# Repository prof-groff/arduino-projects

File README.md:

# arduino-projects

### makeToneBoard Parts List

* 1 x 28-pin DIP Atmel ATmega328p Microcontroller
* 1 x 28-pin DIP socket
* 1 x 7805 5-V linear voltage regulator
* 1 x Lite-On 4301-package 7-segment display
* 1 x 16 MHz Crystal
* 1 x SPST tactile switch/button, normally open, momentarily closed
* 1 x SPDT slide switch
* 1 x 2 rows, 6 positions header
* 1 x female 2.1 mm barrel jack
* 1 x black female banana plug jack
* 1 x red female banana plug jack
* 1 x 300 ohm resistor, 0.25W
* 7 x 110 ohm resistor, 0.25W
* 2 x 100 kohm resistor, 0.25W
* 2 x 22 pF ceramic capacitor, 100V
* 1 x 0.1 microF ceramic capacitor, 50V
* 1 x 0.33 microF ceramic capacitor, 50V

### WaveFormIO Parts List

* Motorola/Freescale MC14489B
* Lite-On LTC-4727JR 4-Digit Display
* ATmega 328P-PU
* 7805
* PTV09A-2020F-A502 Bourns 5k Poteniometer
* PTV09A-2020F-A103 Bourns 10k Poteniometer
* Push Button - Momentary On - Schurter 1301.9305
* E-Switch EG2301A (6mm-tall switch arm)
* 108-0903-001 (Black)
* 108-0902-001 (Red)
* Op-Amp for voltage follower
* TE Connectivity 1-971111-3 Flat Cable 10C 28AWG
* 3365/10-CUT-LENGTH 3M
* OMRON XG4M-1030-T Cable Crip Connector Female
* OMRON XG4C-1031 PCB Socket Male

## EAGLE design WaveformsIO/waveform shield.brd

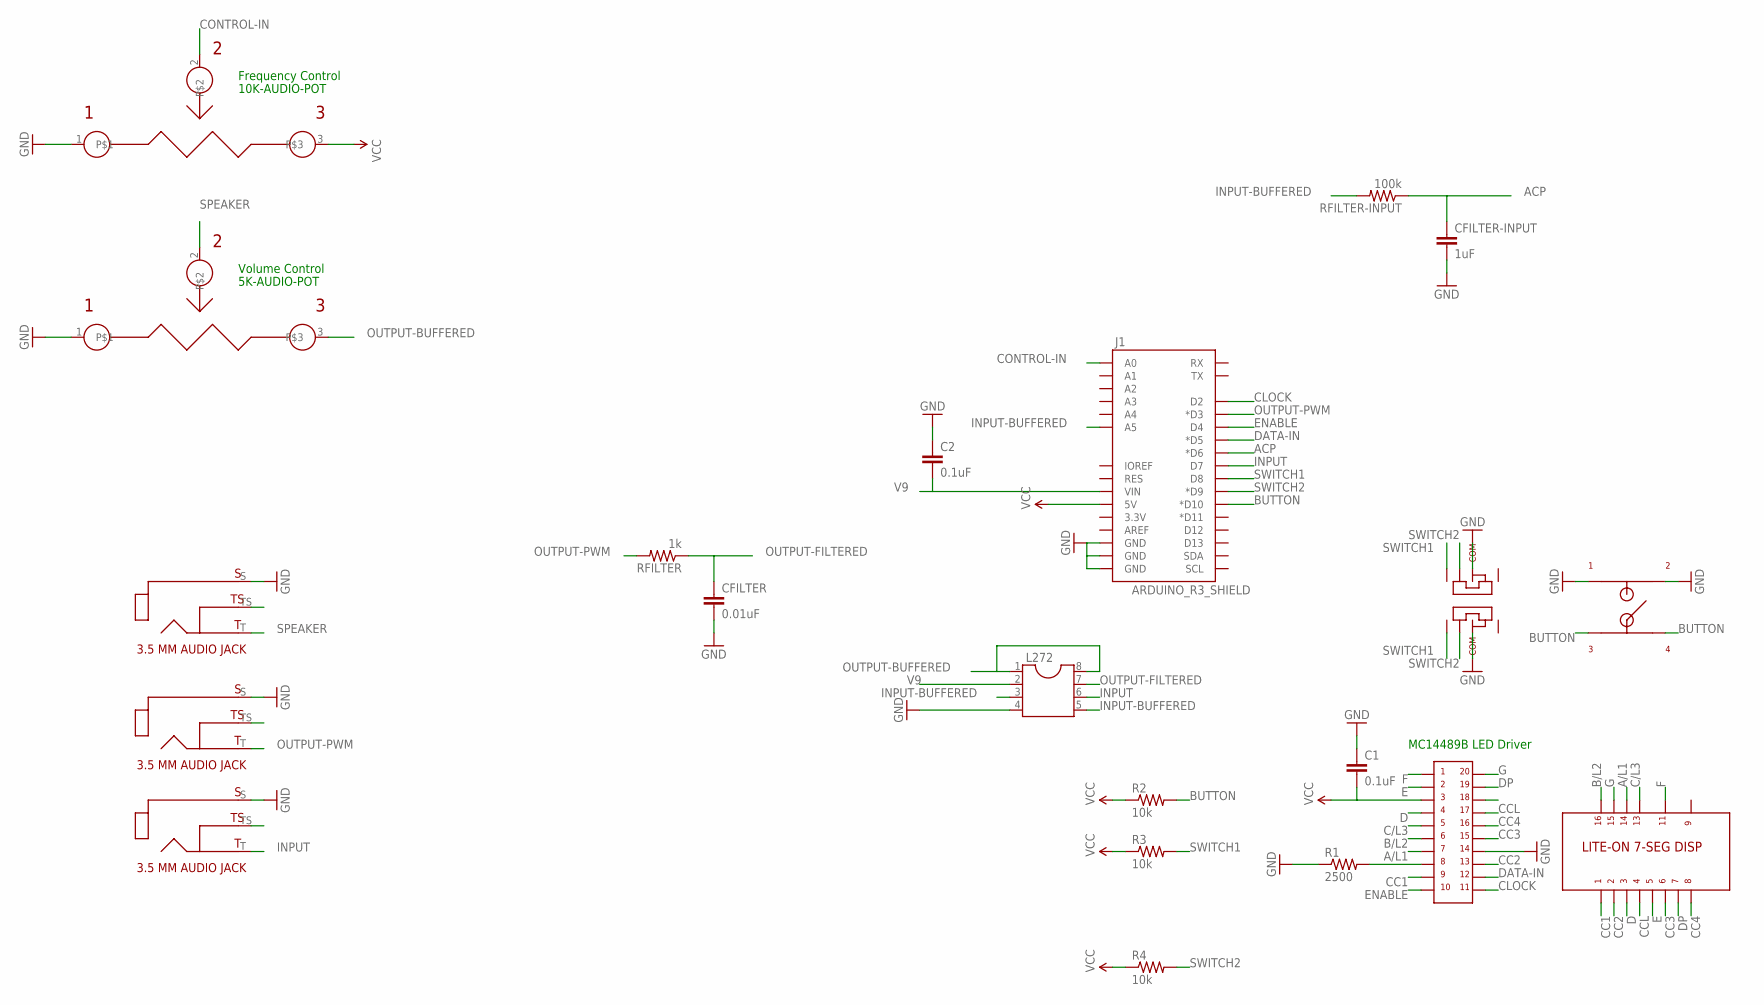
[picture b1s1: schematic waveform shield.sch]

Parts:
5K-AUDIO-POT: BOURNS-PTV09A-2; BOURNS-POT-PTV09A-2
C1, C2: 0.1uF; CAP-PTH-SMALL
CFILTER: 0.01uF; CAP-PTH-SMALL
CFILTER-INPUT: 1uF; CAP-PTH-SMALL
J1: ARDUINO_R3_SHIELD; UNO_R3_SHIELD
L272: DIL8; DIL08
R1: 2500; AXIAL-0.3
R2, R3, R4: 10k; AXIAL-0.3
RFILTER: 1k; AXIAL-0.3
RFILTER-INPUT: 100k; AXIAL-0.3
U$1: LITE-ON-7-SEG-DISP; 7-SEG-DISPLAY-LITE-ON
U$2: MC14489B-LED-DRIVER; DIP-20
U$3, U$6, U$7: 3.5MM-AUDIO-JACK-CUI; 3.5MM-AUDIO-JACK-MONO-CUI
U$4: E-SWITCH-THREE-WAY-SWITCH; EG2301-SLIDE-SWITCH
U$5: SWITCH-MOMENTARY-ON-SCHURTER
U$9: BOURNS-PTV09A-2; BOURNS-POT-PTV09A-2

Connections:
A/L1: U$1.P$14, U$2.P$7
ACP: CFILTER-INPUT.1, J1.D6 (*D6), RFILTER-INPUT.P$1 (1)
B/L2: U$1.P$16, U$2.P$6
BUTTON: J1.D10 (*D10), R2.P$2 (2), U$5.P$3, U$5.P$4
C/L3: U$1.P$13, U$2.P$5
CC1: U$1.P$1, U$2.P$9
CC2: U$1.P$2, U$2.P$13
CC3: U$1.P$6, U$2.P$15
CC4: U$1.P$8, U$2.P$16
CCL: U$1.P$4, U$2.P$17
CLOCK: J1.D2, U$2.P$11
CONTROL-IN: J1.A0, U$9.2
D: U$1.P$3, U$2.P$4
DATA-IN: J1.D5 (*D5), U$2.P$12
DP: U$1.P$7, U$2.P$19
E: U$1.P$5, U$2.P$2
ENABLE: J1.D4, U$2.P$10
F: U$1.P$11, U$2.P$1
G: U$1.P$15, U$2.P$20
GND: 5K-AUDIO-POT.1, C1.1, C2.1, CFILTER.2, CFILTER-INPUT.2, J1.GND@0 (GND), J1.GND@1 (GND), J1.GND@2 (GND), L272.4, R1.P$1 (1), U$2.P$14, U$3.S, U$4.P$3, U$4.P$7, U$5.P$1, U$5.P$2, U$6.S, U$7.S, U$9.1
INPUT: J1.D7, L272.6, U$7.T
INPUT-BUFFERED: J1.A5, L272.3, L272.5, RFILTER-INPUT.P$2 (2)
unnamed: R1.P$2 (2), U$2.P$8
OUTPUT-BUFFERED: 5K-AUDIO-POT.3, L272.1, L272.8
OUTPUT-FILTERED: CFILTER.1, L272.7, RFILTER.P$1 (1)
OUTPUT-PWM: J1.D3 (*D3), RFILTER.P$2 (2), U$6.T
SPEAKER: 5K-AUDIO-POT.2, U$3.T
SWITCH1: J1.D8, R3.P$2 (2), U$4.P$1, U$4.P$5
SWITCH2: J1.D9 (*D9), R4.P$2 (2), U$4.P$2, U$4.P$6
V9: C2.2, J1.VIN, L272.2
VCC: C1.2, J1.5V, R2.P$1 (1), R3.P$1 (1), R4.P$1 (1), U$2.P$3, U$9.3

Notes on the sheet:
MC14489B LED Driver
5K-AUDIO-POT
10K-AUDIO-POT
Volume Control
Frequency Control

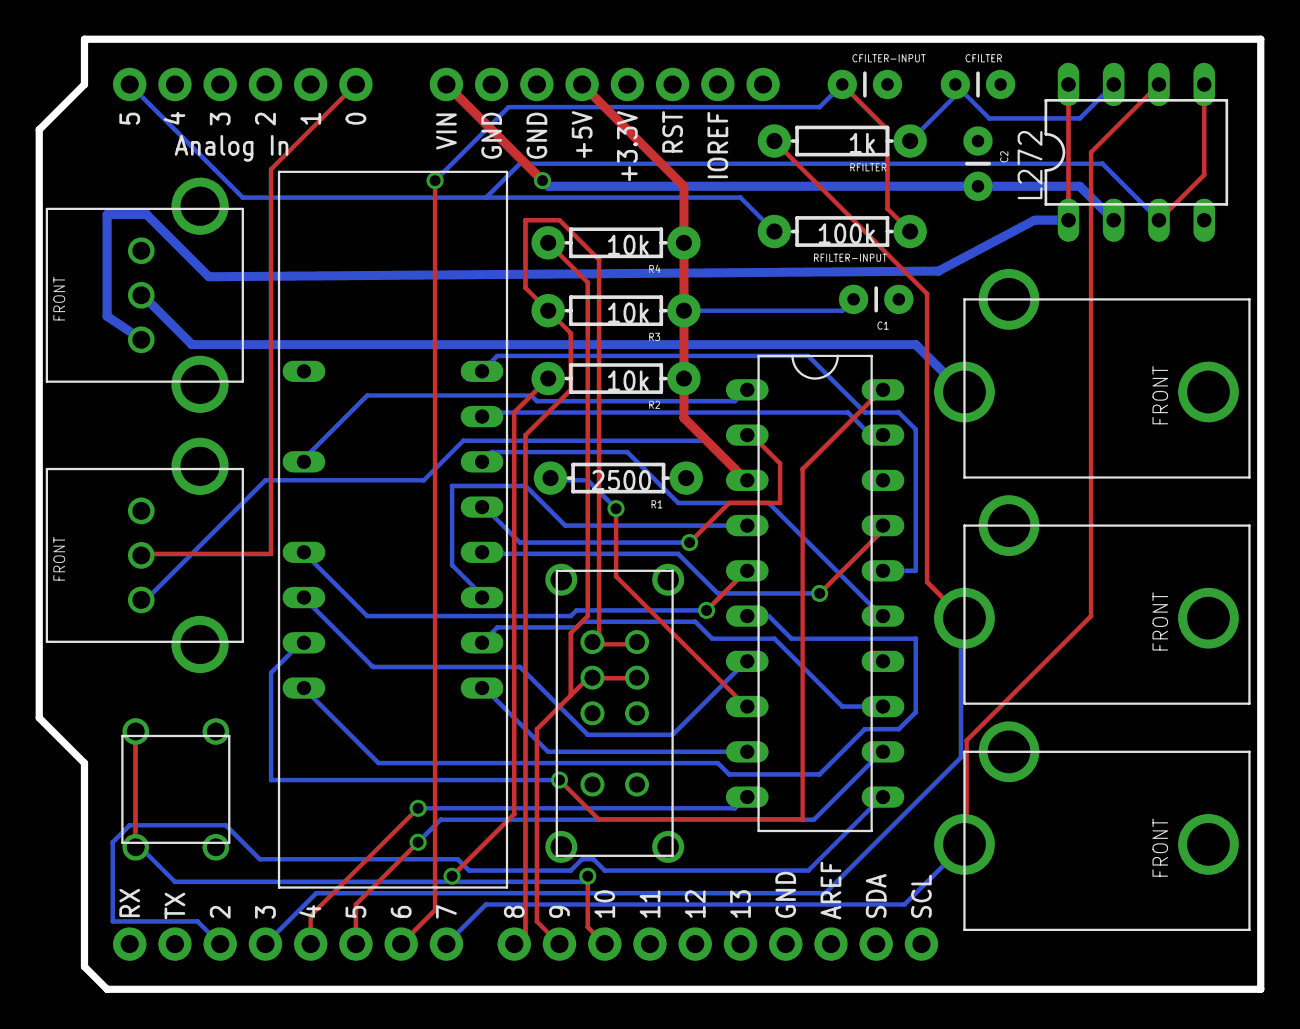
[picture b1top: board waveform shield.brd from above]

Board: 2 copper layers, 68.6 x 53.3 mm, 21 parts (0 on the bottom side), 31 nets.

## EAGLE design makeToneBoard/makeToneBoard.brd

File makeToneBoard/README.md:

# arduino-projects

### makeToneBoard Parts List

* 1 x 28-pin DIP Atmel ATmega328p Microcontroller
* 1 x 28-pin DIP socket
* 1 x 7805 5-V linear voltage regulator
* 1 x Lite-On 4301-package 7-segment display
* 1 x 16 MHz Crystal
* 1 x SPST tactile switch/button, normally open, momentarily closed
* 1 x SPDT slide switch
* 1 x 2 rows, 6 positions header
* 1 x female 2.1 mm barrel jack
* 1 x black female banana plug jack
* 1 x red female banana plug jack
* 1 x 300 ohm resistor, 0.25W
* 7 x 110 ohm resistor, 0.25W
* 2 x 100 kohm resistor, 0.25W
* 2 x 22 pF ceramic capacitor, 100V
* 1 x 0.1 microF ceramic capacitor, 50V
* 1 x 0.33 microF ceramic capacitor, 50V

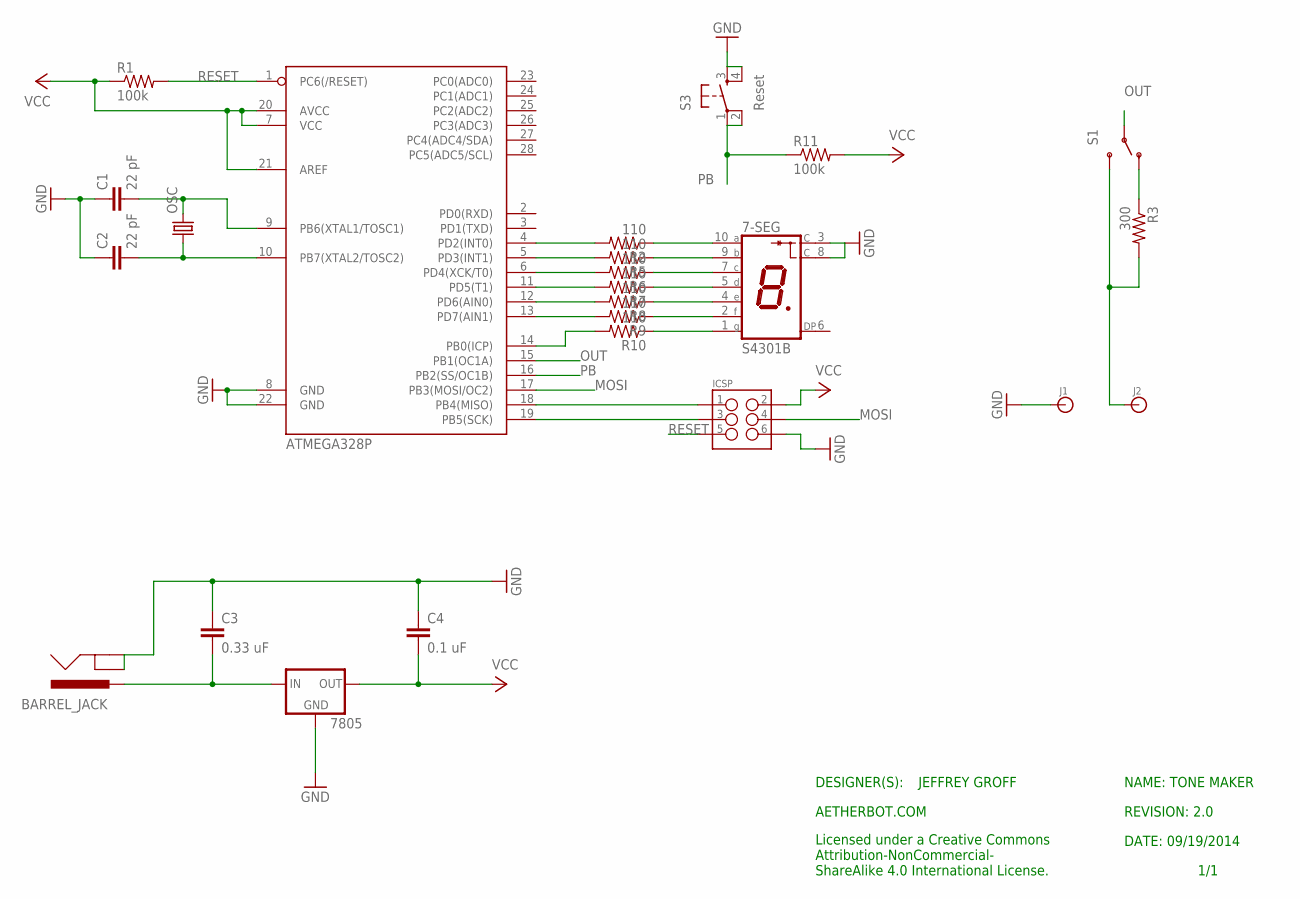
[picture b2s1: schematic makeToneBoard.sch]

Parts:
7-SEG: S4301B
7805: V_REG_78XXSINK; TO220-IGO
BARREL_JACK: POWER_JACKPTH; POWER_JACK_PTH
C1, C2: 22 pF; CAP-PTH-SMALL-KIT
C3: 0.33 uF; CAP-PTH-SMALLEZ
C4: 0.1 uF; CAP-PTH-SMALLEZ
ICSP: M03X2NO_SILK; 2X3-NS
J1, J2: BANANA_CONN
OSC: CRYSTALHC49S; HC49/S
R1, R11: 100k; 0204/7
R2, R5, R6, R7, R8, R9, R10: 110; 0204/7
R3: 300; 0204/7
S1: LED PWR; SWITCH-SPDT
S3: Reset; TACTILE-PTH
U1: ATMEGA328P; DIL28-3

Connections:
GND: 7-SEG.3 (C), 7-SEG.8 (C), 7805.GND, BARREL_JACK.GND, BARREL_JACK.GNDBREAK, C1.1, C2.1, C3.1, C4.1, ICSP.6, J1.P$1, S3.3, S3.4, U1.8 (GND), U1.22 (GND)
MOSI: ICSP.4, U1.17 (PB3(MOSI/OC2))
unnamed: R2.2, U1.4 (PD2(INT0))
unnamed: R3.1, S1.1 (O)
unnamed: J2.P$1, R3.2, S1.3 (S)
unnamed: 7-SEG.1 (G), R10.1
unnamed: C2.2, OSC.1, U1.10 (PB7(XTAL2/TOSC2))
unnamed: 7-SEG.10 (A), R2.1
unnamed: R5.2, U1.5 (PD3(INT1))
unnamed: 7-SEG.9 (B), R5.1
unnamed: R6.2, U1.6 (PD4(XCK/T0))
unnamed: 7805.IN, BARREL_JACK.PWR, C3.2
unnamed: 7-SEG.7 (C), R6.1
unnamed: R7.2, U1.11 (PD5(T1))
unnamed: 7-SEG.5 (D), R7.1
unnamed: ICSP.1, U1.18 (PB4(MISO))
unnamed: ICSP.3, U1.19 (PB5(SCK))
unnamed: R8.2, U1.12 (PD6(AIN0))
unnamed: 7-SEG.4 (E), R8.1
unnamed: R9.2, U1.13 (PD7(AIN1))
unnamed: 7-SEG.2 (F), R9.1
unnamed: R10.2, U1.14 (PB0(ICP))
unnamed: C1.2, OSC.2, U1.9 (PB6(XTAL1/TOSC1))
OUT: S1.2, U1.15 (PB1(OC1A))
PB: R11.1, S3.1, S3.2, U1.16 (PB2(SS/OC1B))
RESET: ICSP.5, R1.2, U1.1 (PC6(/RESET))
VCC: 7805.OUT, C4.2, ICSP.2, R1.1, R11.2, U1.7 (VCC), U1.20 (AVCC), U1.21 (AREF)

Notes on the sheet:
NAME: TONE MAKER
JEFFREY GROFF
DATE: 09/19/2014
DESIGNER(S):
1/1
REVISION: 2.0
AETHERBOT.COM
Licensed under a Creative Commons Attribution-NonCommercial- ShareAlike 4.0 International License.

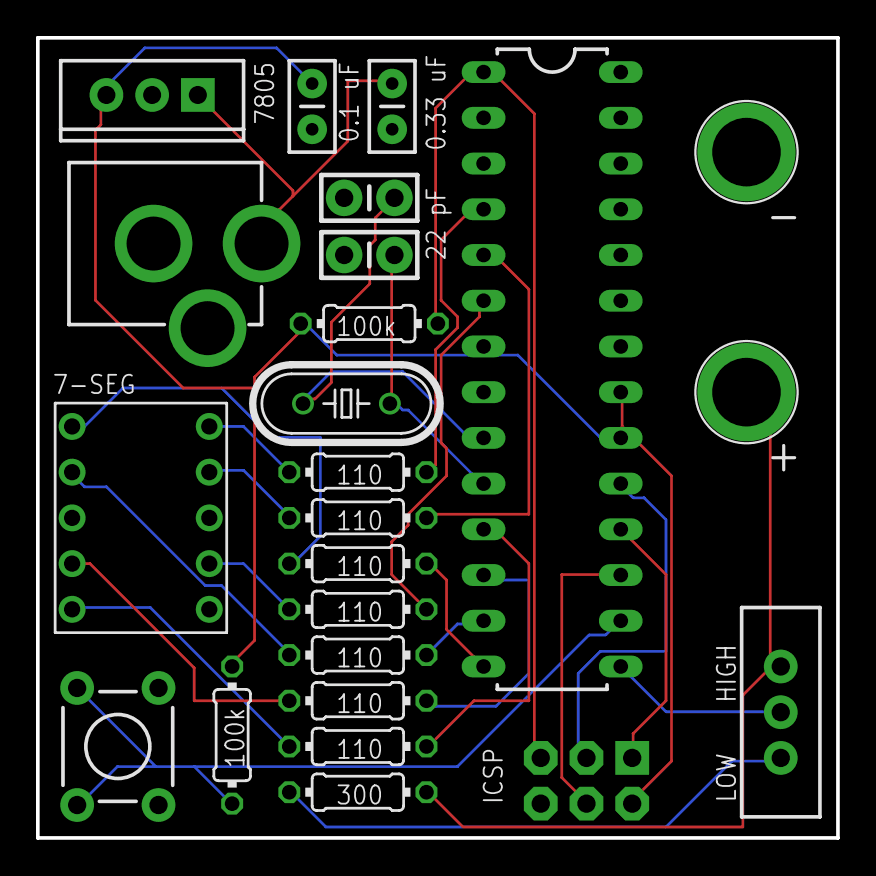
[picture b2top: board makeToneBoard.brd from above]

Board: 2 copper layers, 44.5 x 44.5 mm, 24 parts (0 on the bottom side), 27 nets.

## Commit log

2022-01-28 .gitignore
2022-01-28 WaveformIO
2022-01-28 readme update
2022-01-28 add photo

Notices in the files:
parts and their libraries:
SparkFun-Passives: Licensing: CC v3.0 Share-Alike You are welcome to use this library for commercial purposes.
SparkFun-PowerIC: Licensing: Creative Commons ShareAlike 4.0 International - https://creativecommons.org/licenses/by-sa/4.0
